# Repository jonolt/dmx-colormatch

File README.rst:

DMX-Colormatch
==============

The purpose of this project is to match the colors of color LED fixtures from different manufacturers and output the corresponding dmx values for further use in light control panels.

Especially for low cost LED fixtures often no photometric data is available, which can be imported into professional lighting control consoles to generate exact colors. With small lighting control consoles this is not possible by design. This leads to the situation that colours have to be adjusted manually with a lot of patience, which is still practicable in the HSV colour space as available on mid- and high-range consoles but is hardly practicable in pure RGB color space or with pure DMX values even for an experienced lighting technician.

Firmaware
---------

Approach
^^^^^^^^

A simple rgbc color sensor is used to record the characteristics of a color setting which is then matched by an algorithm on another fixture by systematically varying DMX values. The system is designed to suppress systematic errors by e.g. differences between sensors (which do not need to be calibrated), the algorithm also eliminates influences from the measurement such as the integration time, which varies depending on the light intesistance.

The algorithm tries to minimize the following equation with n colors of the sensor and one clear value that can be the sum of the readings of all the sensors colors or the reading of a clear sensor:

.. image:: https://latex.codecogs.com/gif.latex?x&space;=&space;\sum_{i=0}^n&space;\left(\frac{cur_i}{cur_c}-\frac{ref_i}{ref_c}\right)^2\quad\text{with}\quad&space;xxx_c=\sum_{i=0}^n&space;xxx_i
   :target: https://latex.codecogs.com/gif.latex?x&space;=&space;\sum_{i=0}^n&space;\left(\frac{cur_i}{cur_c}-\frac{ref_i}{ref_c}\right)^2\quad\text{with}\quad&space;xxx_c=\sum_{i=0}^n&space;xxx_i
..
    x = \sum_{i=0}^n \left(\frac{cur_i}{cur_c}-\frac{ref_i}{ref_c}\right)^2\quad\text{with}\quad xxx_c=\sum_{i=0}^n xxx_i

Using relative values eleminates intesity, which would is a systemtical error when the intesity or measuring distance differs between reference and target fixture. With the given sensor with red(r), green(g), blue(b), clear(c) readings the equation is (writen out):

.. image:: https://latex.codecogs.com/gif.latex?x&space;=&space;\left(\frac{cur_r}{cur_c}-\frac{ref_r}{ref_c}\right)^2&plus;\left(\frac{cur_g}{cur_c}-\frac{ref_g}{ref_c}\right)^2&plus;\left(\frac{cur_b}{cur_c}-\frac{ref_b}{ref_c}\right)^2
    :target: https://latex.codecogs.com/gif.latex?x&space;=&space;\left(\frac{cur_r}{cur_c}-\frac{ref_r}{ref_c}\right)^2&plus;\left(\frac{cur_g}{cur_c}-\frac{ref_g}{ref_c}\right)^2&plus;\left(\frac{cur_b}{cur_c}-\frac{ref_b}{ref_c}\right)^2
..
    x = \left(\frac{cur_r}{cur_c}-\frac{ref_r}{ref_c}\right)^2+\left(\frac{cur_g}{cur_c}-\frac{ref_g}{ref_c}\right)^2+\left(\frac{cur_b}{cur_c}-\frac{ref_b}{ref_c}\right)^2

Algorithm
^^^^^^^^^

By using relatiive values the information about the intesity is lost, which is even wanted. This can be solved by making one channel fixed as absolute value, yielding the problem that we do not know which channel will be the highest one. The most robust aproach is to try to minimized x with each of the channels fixed at usually 255 and to take the result with the smallest x value, which wiill then be the best solution.

The Algorithm itself is then quite simple:

.. image:: misc/algorithm_flowchart/algorithm_flowchart.pdf

At the moment there a two stop conditions. Either wenn the x value is very smal or when at a given iteration count. Also the DMX change step will starts with 5 and will decrease to 1 after 5 iterations. This logic will later be the main factor to minimize the matching time.

Current and Planned Features
^^^^^^^^^^^^^^^^^^^^^^^^^^^^

The funtionality will be available via a serial interface and a hardware interface (button and displays).

- [x] parametrize a fixture by sending sensor reading to PC
- [x] take reference colors, which will be matched by ...
- [x] colormatch function (fixture must be conected to dmx output)
- [ ] multiple reference color slots
- [x] programmable start address (usefull at installed fixtures)

Hardware
--------

work in progress

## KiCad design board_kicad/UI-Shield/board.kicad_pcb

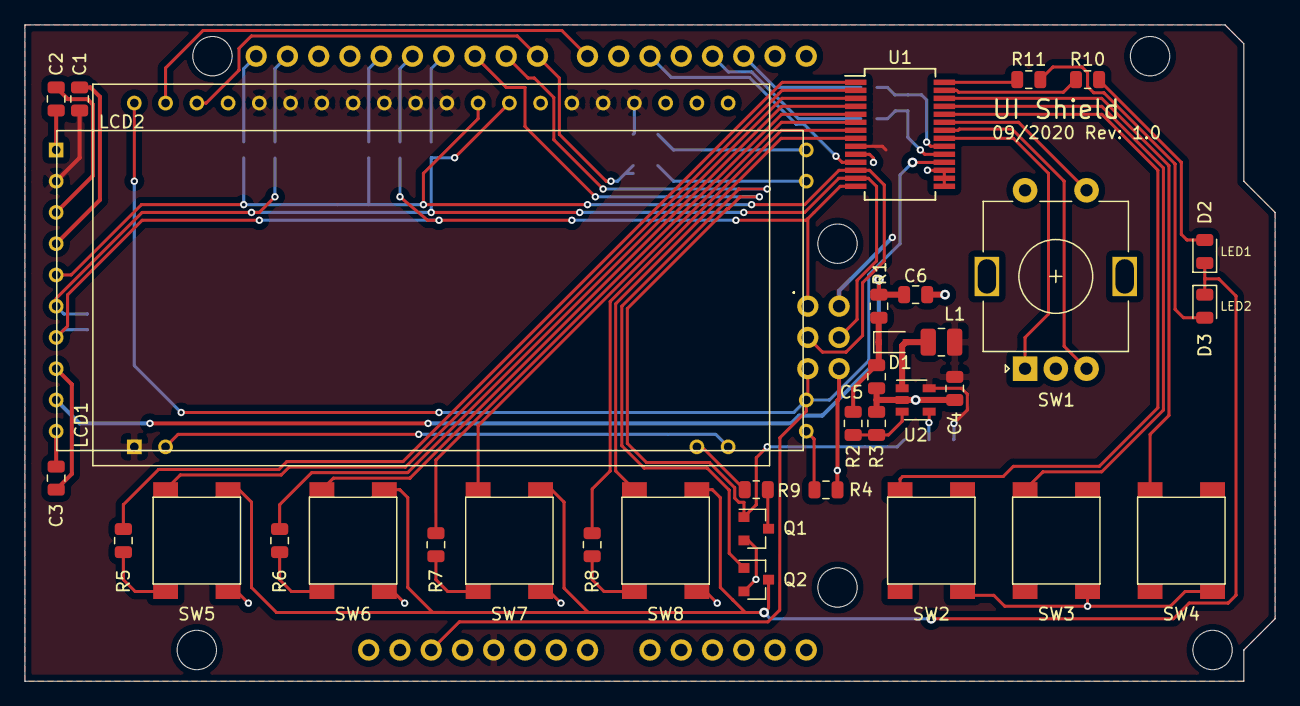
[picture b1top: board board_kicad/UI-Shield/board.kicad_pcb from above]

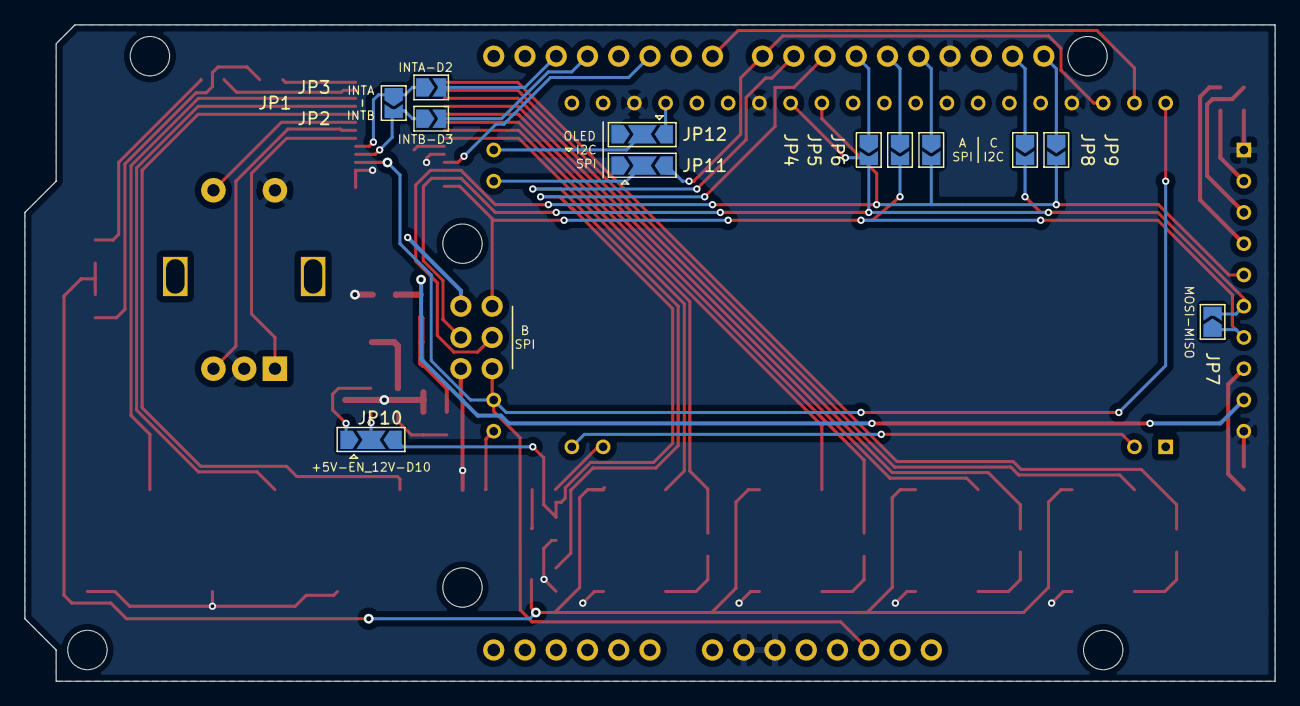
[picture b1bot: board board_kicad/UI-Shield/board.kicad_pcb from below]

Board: 2 copper layers, 101.6 x 53.3 mm, 48 parts (12 on the bottom side), 57 nets.

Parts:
C1, C2: 100n; C_0805_2012Metric
C3, C6: 2.2u; C_0805_2012Metric
C4: 4.7u; C_0805_2012Metric
C5: 1u; C_0805_2012Metric
D1: BAT54J; D_SOD-323F
D2, D3: LED; LED_0805_2012Metric
JP1, JP2, JP3, JP4, JP5, JP6, JP7, JP8, JP9: SolderJumper_2_Open; SolderJumper-2_P1.3mm_Open_TrianglePad1.0x1.5mm
JP10, JP11, JP12: SolderJumper_3_Open; SolderJumper-3_P2.0mm_Open_TrianglePad1.0x1.5mm
L1: 33uH; L_1008_2520Metric
LCD1: EA_DOGM163_with_LED; DOGM162_with_LED
LCD2: EA_OLEDM204; OLEDM204_6GGA
Q1, Q2: BSR14; SOT-23
R1: 100; R_0805_2012Metric
R2: 240k; R_0805_2012Metric
R3: 27k; R_0805_2012Metric
R4: 910k; R_0805_2012Metric
R5, R6, R7, R8: 150; R_0805_2012Metric
R9: 20; R_0805_2012Metric
R10, R11: 560; R_0805_2012Metric
SW1: 1; RotaryEncoder_Alps_EC11E-Switch_Vertical_H20mm
SW2, SW3, SW4: SW_Push; Marquardt_3006_Series
SW5, SW6, SW7, SW8: SW_Push_LED; Marquardt_3006_Series
U1: MCP23S17_SS; SSOP-28_5.3x10.2mm_P0.65mm
U2: LM2705; SOT-23-5
XA1: Arduino_Shield; Arduino_Shield_Large

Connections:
+5V: C1.1, C4.1, JP10.1, JP12.1, L1.1, LCD1.1, LCD1.24, LCD1.25, LCD1.26, LCD1.30, LCD1.31, LCD1.32, LCD1.33, LCD1.34, LCD1.35, LCD1.36, LCD2.2, U1.9, U2.5, XA1.5V1, XA1.5V2
+12V: C6.2, LCD2.9, R1.1
/12V_EN: JP10.2, U2.4
/A: SW1.A, U1.21
/B: SW1.B, U1.22
/BS1: JP12.2, LCD2.20
/D2: JP3.2, XA1.D2
/D3: JP2.2, XA1.D3
/IO_CS: U1.11, XA1.D5
/IO_INTA: JP1.1, JP3.1, U1.20
/IO_INTB: JP1.2, JP2.1, U1.19
/LCD_CS: JP11.3, LCD1.38, XA1.D8
/LCD_LED: JP10.3, Q1.1, XA1.D10
/LCD_RS: LCD1.39, XA1.D7
/LED1: R10.1, U1.27
/LED2: R11.1, U1.28
/LED5: R5.1, U1.1
/LED6: R6.1, U1.3
/LED7: R7.1, U1.5
/LED8: R8.1, U1.7
/MISO: JP5.2, JP7.1, LCD2.7, U1.14, XA1.MISO
/MOSI: JP4.2, JP7.2, JP8.2, LCD1.28, LCD2.6, U1.13, XA1.MOSI
/SCK: JP6.2, JP9.2, LCD1.29, LCD2.5, U1.12, XA1.SCK
/SCL: JP9.1, XA1.SCL
/SDA: JP8.1, XA1.SDA
/SW1: SW1.S1, U1.23
/SW2: SW2.2, U1.24
/SW3: SW3.2, U1.25
/SW4: SW4.2, U1.26
/SW5: SW5.2, U1.2
/SW6: SW6.2, U1.4
/SW7: SW7.2, U1.6
/SW8: SW8.2, U1.8
/SW_LED: Q2.1, XA1.D9
/_LCD_CS: JP11.2, LCD2.19
/~RESET: LCD1.40, LCD2.12, U1.18, XA1.RST1, XA1.RST2
GND: C2.2, C3.2, C4.2, C5.1, C6.1, JP11.1, JP12.3, LCD1.23, LCD1.27, LCD1.37, LCD2.1, LCD2.10, Q1.2, Q2.2, R3.2, R4.1, SW1.C, SW1.S2, SW2.1, SW3.1, SW4.1, SW5.1, SW6.1, SW7.1, SW8.1, U1.10, U1.15, U1.16, U1.17, U2.2, XA1.GND1, XA1.GND2, XA1.GND3, XA1.GND4
unnamed: C1.2, LCD2.4
unnamed: C2.1, LCD2.3
unnamed: C3.1, LCD2.8
unnamed: C5.2, D1.1, R1.2, R2.1
unnamed: D1.2, L1.2, U2.1
unnamed: D2.1, D3.1, Q2.3, SW5.3, SW6.3, SW7.3, SW8.3
unnamed: D2.2, R10.2
unnamed: D3.2, R11.2
unnamed: JP4.1, XA1.D11
unnamed: JP5.1, XA1.D12
unnamed: JP6.1, XA1.D13
unnamed: LCD1.2, LCD1.20
unnamed: LCD1.19, R9.2
unnamed: LCD2.11, R4.2
unnamed: Q1.3, R9.1
unnamed: R2.2, R3.1, U2.3
unnamed: R5.2, SW5.4
unnamed: R6.2, SW6.4
unnamed: R7.2, SW7.4
unnamed: R8.2, SW8.4

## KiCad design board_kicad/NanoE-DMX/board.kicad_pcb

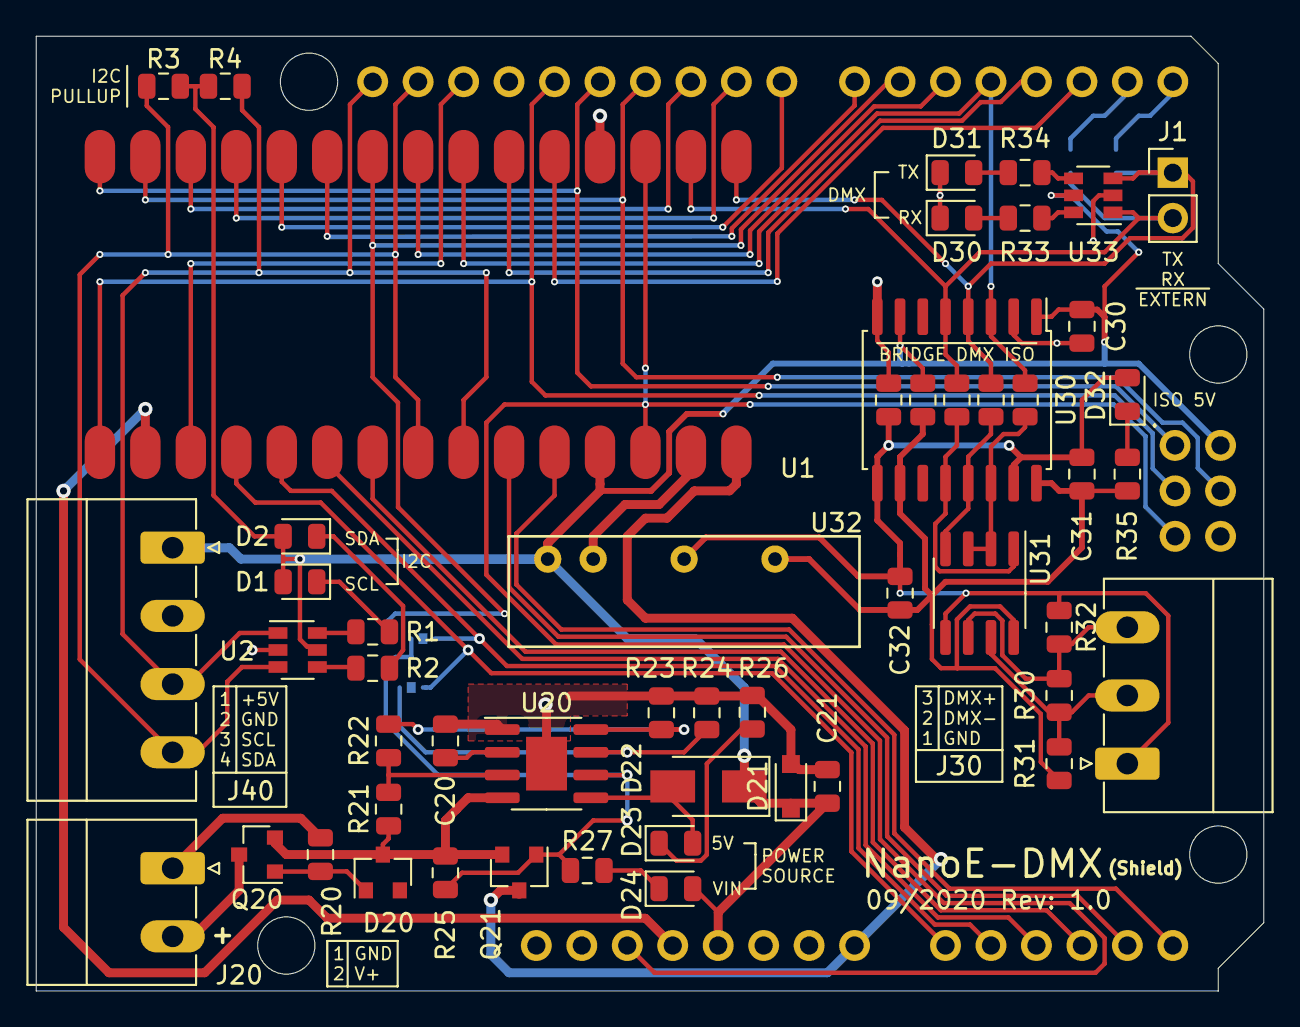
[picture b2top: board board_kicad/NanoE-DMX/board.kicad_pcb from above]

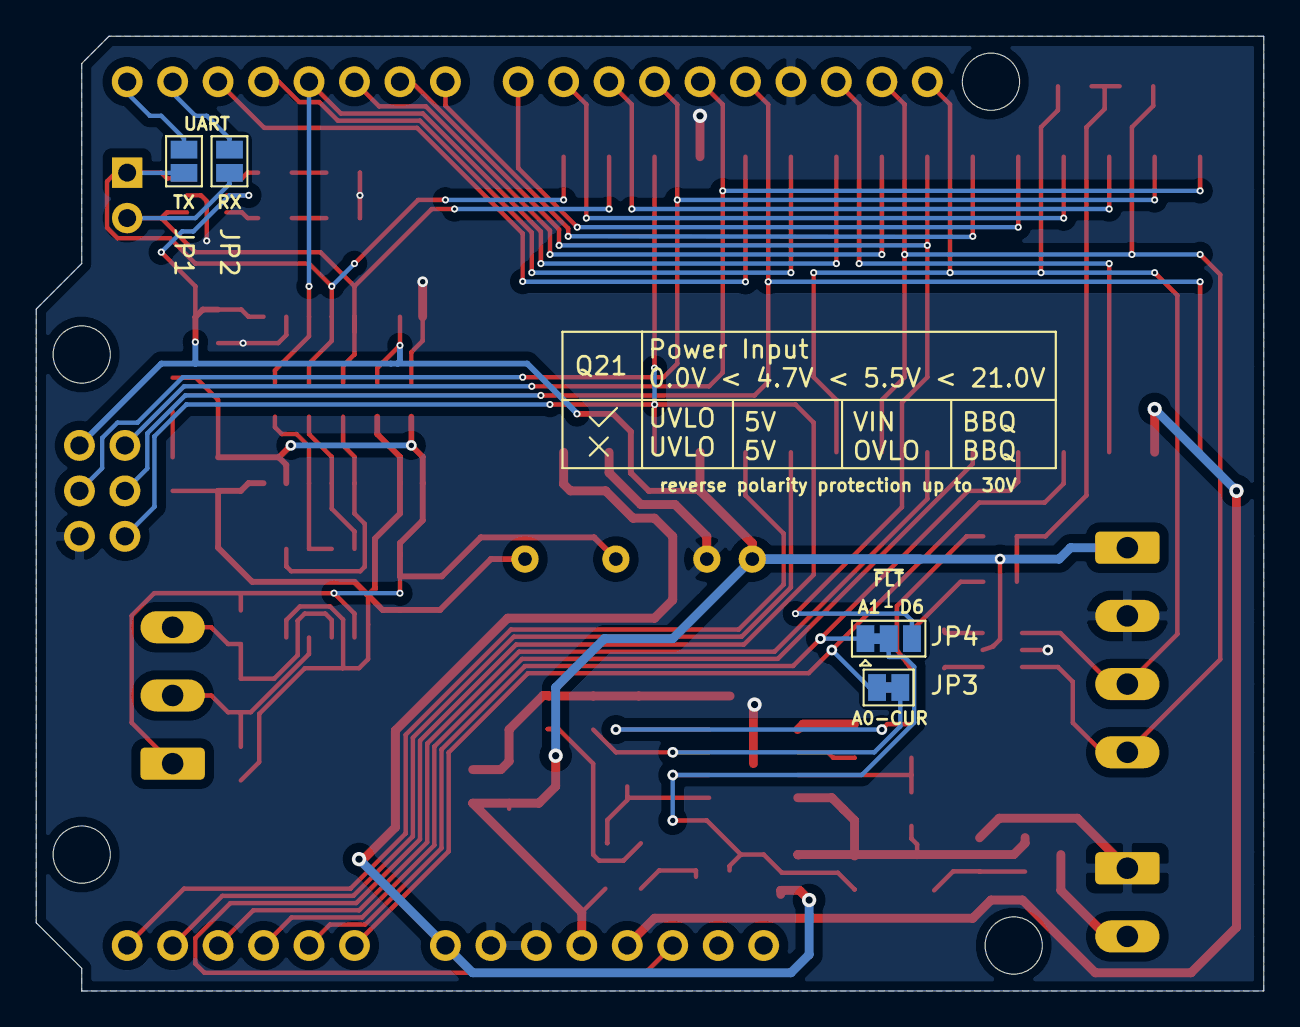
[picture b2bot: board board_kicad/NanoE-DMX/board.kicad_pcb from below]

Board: 2 copper layers, 68.6 x 53.3 mm, 56 parts (4 on the bottom side), 57 nets.

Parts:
C20: 2.2n; C_0805_2012Metric
C21: 1u; C_0805_2012Metric
C30, C31: 100n; C_0805_2012Metric
C32: 10u; C_0805_2012Metric
D1, D2, D30, D31: LED yellow; LED_0805_2012Metric
D20: BZX84C15; D_SOT-23_ANK
D21: BAT54J; D_SOD-323_HandSoldering
D22: STPS1L30AFN; D_SMA
D23: LED orange; LED_0805_2012Metric
D24: LED green; LED_0805_2012Metric
D32: LED red; LED_0805_2012Metric
J1: Conn_01x02; PinHeader_1x02_P2.54mm_Vertical
J20: Conn_01x02; PhoenixContact_MC_1,5_2-G-3.81_1x02_P3.81mm_Horizontal
J30: Conn_01x03; PhoenixContact_MC_1,5_3-G-3.81_1x03_P3.81mm_Horizontal
J40: Conn_01x04; PhoenixContact_MC_1,5_4-G-3.81_1x04_P3.81mm_Horizontal
JP1, JP2: SolderJumper_2_Open; SolderJumper-2_P1.3mm_Open_Pad1.0x1.5mm
JP3: SolderJumper_2_Bridged; SolderJumper-2_P1.3mm_Bridged_Pad1.0x1.5mm
JP4: SolderJumper_3_Bridged12; SolderJumper-3_P1.3mm_Bridged12_Pad1.0x1.5mm
Q20, Q21: IRLM5203 (PMOS_GSD); SOT-23
R1, R2, R26, R27, R33, R34, R35: 1k; R_0805_2012Metric
R3, R4: 10k; R_0805_2012Metric
R20, R25: 100k; R_0805_2012Metric
R21: 130k; R_0805_2012Metric
R22: 6.8k; R_0805_2012Metric
R23: 39k; R_0805_2012Metric
R24: 910; R_0805_2012Metric
R30: 120; R_0805_2012Metric
R31, R32: 560; R_0805_2012Metric
R130, R131, R132, R133, R134: 0; R_0805_2012Metric
U1: Arduino_Nano_Every; Nano_Every_SMD
U2, U33: 74LVC2G34; SOT-23-6
U20: TPS259630; SOIC-8-1EP_3.9x4.9mm_P1.27mm_EP2.29x3mm
U30: ADUM1301; SOIC-16W_7.5x10.3mm_P1.27mm
U31: MAX487E; SOIC-8_3.9x4.9mm_P1.27mm
U32: RFB-0505S; SIP7-1-2-4-6
XA1: Arduino_Uno_Shield; Arduino_Shield

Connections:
+3V3: U1.17, XA1.3V3
+5V: C21.1, C30.2, D1.2, D2.2, D21.1, D22.1, D24.2, J40.1, R3.1, R4.1, R133.2, U1.27, U2.5, U30.1, U30.7, U32.1, U33.5, XA1.5V1, XA1.5V2
/A0-CUR: JP3.2, U1.19, XA1.A0
/A1-~FLT: JP4.1, U1.20, XA1.A1
/A2: U1.21, XA1.A2
/A3: U1.22, XA1.A3
/A4: U1.25, XA1.A4
/A5: U1.26, XA1.A5
/AREF: U1.18, XA1.AREF
/CUR: JP3.1, R24.1, U20.7
/D2: U1.5, XA1.D2
/D3: U1.6, XA1.D3
/D6-~FLT: JP4.3, U1.9, XA1.D6
/D9: U1.12, XA1.D9
/DMX+: J30.3, R30.2, R32.1, U31.6
/DMX-: J30.2, R30.1, R31.2, U31.7
/IO_CS: U1.8, XA1.D5
/ISO_+5V: C31.1, C32.2, R31.1, R35.1, R133.1, U30.10, U30.16, U31.8, U32.6
/ISO_GND: C31.2, C32.1, D32.2, J30.1, R32.2, R134.1, U30.9, U30.15, U31.5, U32.4
/ISO_REDE: R130.1, U30.14, U31.2, U31.3
/ISO_RX: R132.1, U30.12, U31.1
/ISO_TX: R131.1, U30.13, U31.4
/LCD_CS: U1.11, XA1.D8
/LCD_LED: U1.13, XA1.D10
/LCD_RS: U1.10, XA1.D7
/MISO: U1.15, XA1.D12, XA1.MISO
/MOSI: U1.14, XA1.D11, XA1.MOSI
/REDE: R130.2, U1.7, U30.3, XA1.D4
/RX: J1.2, JP2.1, R132.2, U1.2, U30.5, U33.1
/SCK: U1.16, XA1.D13, XA1.SCK
/SCL: J40.3, R4.2, U1.24, U2.1, XA1.SCL
/SDA: J40.4, R3.2, U1.23, U2.3, XA1.SDA
/TX: J1.1, JP1.1, R131.2, U1.1, U30.4, U33.3
/VCC_EXT: D20.1, Q20.2, Q21.2, R21.1, R25.1, U20.4
/VCC_IN: J20.2, Q20.3
/VIN: Q21.3, U1.30, XA1.VIN
/~FLT: JP4.2, Q21.1, R25.2, R27.1, U20.6
/~RESET: U1.3, U1.28, XA1.RST1, XA1.RST2
GND: C20.2, C21.2, C30.1, D21.2, D30.1, D31.1, J20.1, J40.2, R20.2, R23.2, R24.2, R26.1, R134.2, U1.4, U1.29, U2.2, U20.1, U20.9, U30.2, U30.8, U32.2, U33.2, XA1.GND1, XA1.GND2, XA1.GND3, XA1.GND4
unnamed: C20.1, U20.2
unnamed: D1.1, R1.1
unnamed: D2.1, R2.1
unnamed: D20.2, Q20.1, R20.1
unnamed: D22.2, D23.2, U20.5
unnamed: D23.1, R26.2
unnamed: D24.1, R27.2
unnamed: D30.2, R33.1
unnamed: D31.2, R34.1
unnamed: D32.1, R35.2
unnamed: JP1.2, XA1.D0
unnamed: JP2.2, XA1.D1
unnamed: R1.2, U2.6
unnamed: R2.2, U2.4
unnamed: R21.2, R22.1, U20.3
unnamed: R22.2, R23.1, U20.8
unnamed: R33.2, U33.6
unnamed: R34.2, U33.4

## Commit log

2020-05-23 initial commit, fsm
2020-07-09 fixturematch works for parametrizing with fsm
2020-07-09 added script for parametrize, bugfixes
2020-07-13 coloralgorithm in python working
2020-07-16 algorithm not woking in all cases
2020-07-16 algorithm works
2020-07-16 further algorithm improvements
2020-07-17 new alogrithm working
2020-07-17 chnaged reference for rel dif to c
    this improves performance of algorithm significantly
2020-07-24 added buttons for ref and match, autoformated code
2020-07-24 renamed firmware folders, added README
2020-08-04 initial kicad commit, with basic circuits
2020-08-09 sch and pcb for main board designed
2020-08-21 extended, improved and finished circuits and boards
    also added PDF and renders of shematic/board
    INFO: The Displays Library is not included and can be found at
    https://github.com/jonolt/KiCad_lib_EA-Dispaly
2020-08-21 renamed KiCad project directories to board names
2020-08-21 updated README with flowchart
2020-08-23 added values and manufacurer id (kicost), improvements
    BOTH
    - added missing values for resitors and diodes
    - added manf# for calculating and ordering with kicost
    - minor improvements
    NanoE-dmx
    - bus controll LEDs (buffered) fixed for TX/RX, SDA/SCL
2020-08-27 minor cleanup
2020-08-30 started implementing new structure from scratch
2020-09-07 fixed minor mistakes, but U1 footprint is still wrong
    - silkscreen of C21 and D21
    - added connector pin description
    - wrong footprint (was without thermal pad) for U20
    - U20 (TPS259630) footrpint association also fixed in library
    - silkscreen Power Source swapped
    - C32 replaced tantal with ceramic condesnator (polarity was wrong)
2020-09-07 basics of DMX, Sensor and Serial works
2020-09-07 commit lib automaton
2020-09-26 fixed errors in NanoE-DMX and UI-Shield
    NanoE-DMX -> Rev: 1.0:
    - see previous commit
    - fixed footprint of U1
    - reroutet corresponding tracks
    - added ICSP header to board
    UI-Shield -> Rev: 1.0:
2020-10-10 implemented basic python gui and serial communication
2020-10-10 removed code and files associated with the UI-Shield
    the core libraries for the shield itself will be developed
    in another branch as working hardware (in the needed combination)
    is not availbale yet. The PC UI in this branch should be
    enough atm and was planned anyways.
2020-10-18 implemented color match algorithm and cleaned up code
    - improved variable naming
    - registers do not work
    - added mainmachione source files to git (previously forgotten)
2020-11-05 ploting works but bad performance
2021-02-28 reworked tkui, defined commands
    Reworked the tkui to be used without
    the UI-Shield buttons as remote controll.
    The UI-Shield will be implemented as remote
    interface getting the lcd text send to and
    sending the button presses to the controller.
    Reworked Plotting but still bad performance,
